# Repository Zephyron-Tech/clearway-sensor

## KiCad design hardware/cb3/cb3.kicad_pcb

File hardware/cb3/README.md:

# CB3 – nosná deska ClearWay v3 (KiCad 10)

Kompletní návrh desky do skříně střešního skeneru v3: schéma, plošný spoj a výrobní data. Popis funkce, bloků a pinů: [configurator/docs/v3-deska.md](../../configurator/docs/v3-deska.md).

> **Stav: rev. B, prototyp.** Schéma i deska prošly kontrolami (ERC 0 chyb, DRC 0 nespojení a 0 kolizí). Návrh vznikl automaticky ze zapojení podle datasheetů a deska je vedená autorouterem. **Před objednávkou ho musí zkontrolovat člověk s praxí v návrhu DPS**, viz [Co zkontrolovat před výrobou](#co-zkontrolovat-před-výrobou).

## Deska

| | |
|---|---|
| Rozměr | 242 × 162 mm, 1,6 mm, obrys s výřezy pro sloupky víka a 4 otvory M3 |
| Vrstvy | 4: F.Cu signály, In1.Cu zem, In2.Cu napájení (VIN_P, 5 V) a signály, B.Cu signály a zem |
| Součástky | 214 (90 C, 51 R, 13 IO, CM5, ZED-F9R, M.2 modem …). Nahoře velké díly, **dole 70 pasivních součástek** (oboustranné osazení) |
| Spoje | 8,8 m spojů, ~500 prokovů 0,5/0,25 mm |
| Pravidla | min. spoj 0,1 mm, mezera 0,125 mm, vrták 0,2 mm (běžná 4vrstvá výroba JLCPCB/PCBWay) |
| Třídy sítí (spoj / mezera) | Default 0,13 / 0,125 mm; Diff (Ethernet, USB) 0,2 / 0,125; Power 0,4 / 0,15; Power12 0,8 / 0,2; HV (vstup) 1,0 / 0,2; Switch (uzly měničů) 0,8 / 0,2 |

Spodní strana: [cb3-bottom.png](cb3-bottom.png), pohled 3D: [cb3-iso.png](cb3-iso.png).

## Výrobní data

Složka [vyroba/](vyroba/):

| Soubor | Co to je |
|---|---|
| `cb3-gerber.zip` | Gerber všech 4 vrstev mědi, masky, pasty, potisku a obrysu + vrtání Excellon (PTH a NPTH zvlášť). Tohle se nahraje výrobci. |
| `cb3-osazeni.csv` | souřadnice pro osazovací automat (obě strany, 201 položek; montážní otvory a testovací plošky se neosazují) |
| `cb3-kusovnik.csv` | kusovník seskupený podle hodnoty, pouzdra a typu (sloupec MPN) |
| `cb3-schema.pdf` | schéma, 6 listů |
| `cb3-osazeni-top.pdf` | osazovací výkres horní strany |

Znovu vygenerovat (po změně v KiCadu):

```bash
sh configurator/scripts/kicad/fab.sh
```

**Objednávka u JLCPCB (příklad):** 4 vrstvy, 1,6 mm, standardní skladba JLC04161H-7628, HASL nebo ENIG (ENIG doporučené kvůli jemné rozteči CM5 a M.2). CM5, modul ZED-F9R a modem EM05-G je levnější dodat a osadit ručně.

## Co v projektu je

| Soubor | Obsah |
|---|---|
| `cb3.kicad_pro` | projekt a třídy sítí |
| `cb3.kicad_sch` + `napajeni`, `vypocet`, `site`, `radio`, `obsluha` | přehledový list a 5 listů bloků |
| `cb3.kicad_pcb` | deska |
| `cb3.kicad_sym`, `cb3.pretty/` | vlastní symboly (KSZ8795CLX, ZED-F9R, TPS1H100A, CM5) a pouzdra (CM5 z referenčního projektu Raspberry Pi, M.2 Key B) |
| `netlist.json` | zapojení po vývodech, ze kterého vzniká schéma i deska |

## Jak deska vznikla (skripty v `configurator/scripts/kicad/`)

1. `cb3-design.mjs`: zapojení všech součástek podle doporučených zapojení z datasheetů (zdroje v hlavičce souboru).
2. `gen-full.mjs`: schéma a `netlist.json`. ERC 0 chyb.
3. `gen-pcb-full.py place`: rozmístění (konektory u otvorů ve skříni, pasivy u svých IO, část na spodní straně), zóny a zakázané oblasti.
4. Freerouting 1.9 (export DSN / import SES), pak `finish-route.py`: vlastní dotahovač (A* na mřížce 0,1 mm) na posledních několik spojů a opravy kolizí.
5. `gen-pcb-full.py pour`: rozlití zemí a zón, `link-pcb.py`: svázání pouzder se symboly schématu (funguje F8 Aktualizovat DPS ze schématu).
6. `fab.sh`: výrobní data.
7. `export-3d.py`: polohy a rozměry součástek do 3D modelu v konfigurátoru (`src/cad/board-v3-pcb.js`).
8. `export-texture.py`: měď, plošky a potisk obou stran jako textura desky v konfigurátoru (`public/models/cb3-top.jpg`, `cb3-bottom.jpg`).

**Od teď je zdrojem pravdy projekt KiCad.** Úpravy dělat v KiCadu ručně; generátory desku přepíší (rozmístění a vedení by se ztratilo).

## Kontroly

- **ERC:** 0 chyb, 0 varování.
- **DRC:** 0 nespojených sítí, 0 kolizí, 0 zkratů. Zbývá jen kosmetika potisku (popisky se překrývají nebo leží na ploškách, ~90 varování; výrobce potisk na ploškách ořízne).
- **Parita DPS ↔ schéma:** 17 varování, všechny jsou upevňovací a stínicí plošky konektorů (MP, SH, S1, S2), které jsou záměrně na zemi a symbol je nemá.

## Co zkontrolovat před výrobou

Seřazené podle důležitosti.

1. **Zemní vrstva In1 není souvislá.** Autorouter jí vedl asi 3,4 m signálů. Návratové cesty, rušení a GNSS tím trpí. Nejlepší oprava je převést tyto spoje na F/B/In2 a In1 nechat jako celistvou zem.
2. **Diferenciální páry** (Ethernet T1–T5, USB k modemu a servisu) jsou vedené bez řízené impedance a bez vyrovnání délek. Pro 100 Mb/s a USB 2.0 by to fungovat mělo, ale páry je potřeba projít a podle skladby výrobce nastavit šířku/mezeru na 100 Ω a 90 Ω.
3. **RF GNSS** (J7 → ZED-F9R RF_IN): spoj má mít 50 Ω (koplanár se zemí) a pod modulem souvislou zem.
4. **Větev 12 V je jen snižující** (TPS54560B). Při napětí vozu pod ~13 V (12V vůz, startování) klesne pod 12 V. Ověřit, že skenery a lidar snesou rozsah 9–12 V, jinak měnič buck-boost.
5. **Pouzdro M.2 Key B** je odvozené z pouzdra M-key z referenčního projektu CM5 (posunutý klíč). Před objednáním porovnat s výkresem TE 2199230-3.
6. **Hodnoty pasivních součástek** jsou podle referenčních návrhů TI. U U2 (12 V) je kompenzace přepočítaná, ověřit v TI WEBENCH nebo výpočtem.
7. **Teplo:** U3 (5 V / 5 A) a U2 potřebují tepelné prokovy do zemních vrstev, zkontrolovat počet pod plochou pouzdra.
8. **Ethernet CM5 ↔ přepínač** jde přes dva transformátory zády k sobě (T4, T5). Funkční, ale ověřit proti aplikační poznámce Microchip.
9. **Potisk:** přesunout překrývající se popisky (kosmetika).

## Jak to otevřít

KiCad je v `~/Applications/KiCad` (instalace přes Homebrew chtěla heslo správce). Otevřít `cb3.kicad_pro`, při prvním spuštění potvrdit výchozí knihovny.

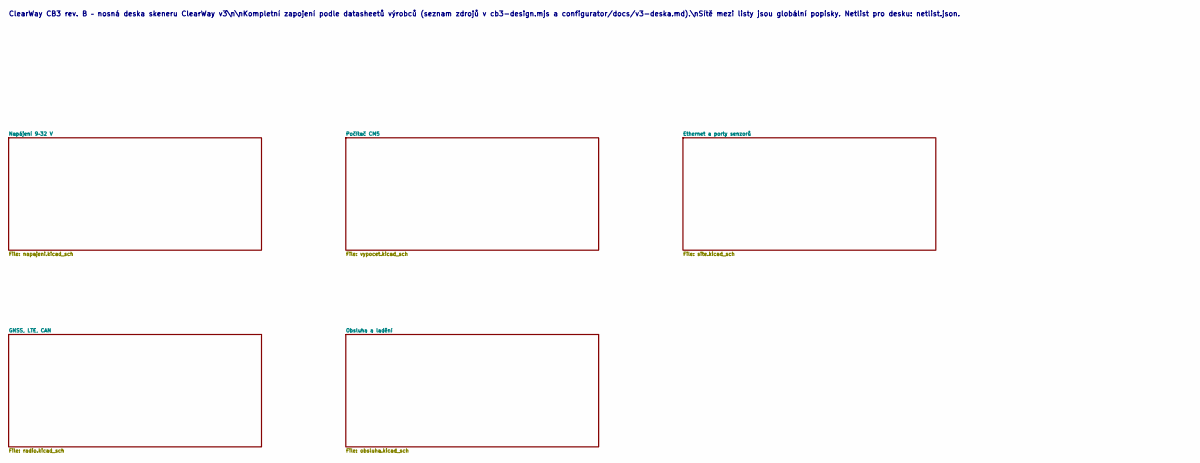
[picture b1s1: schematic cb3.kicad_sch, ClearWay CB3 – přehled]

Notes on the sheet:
ClearWay CB3 rev. B – nosná deska skeneru ClearWay v3\n\nKompletní zapojení podle datasheetů výrobců (seznam zdrojů v cb3-design.mjs a configurator/docs/v3-deska.md).\nSítě mezi listy jsou globální popisky. Netlist pro desku: netlist.json.

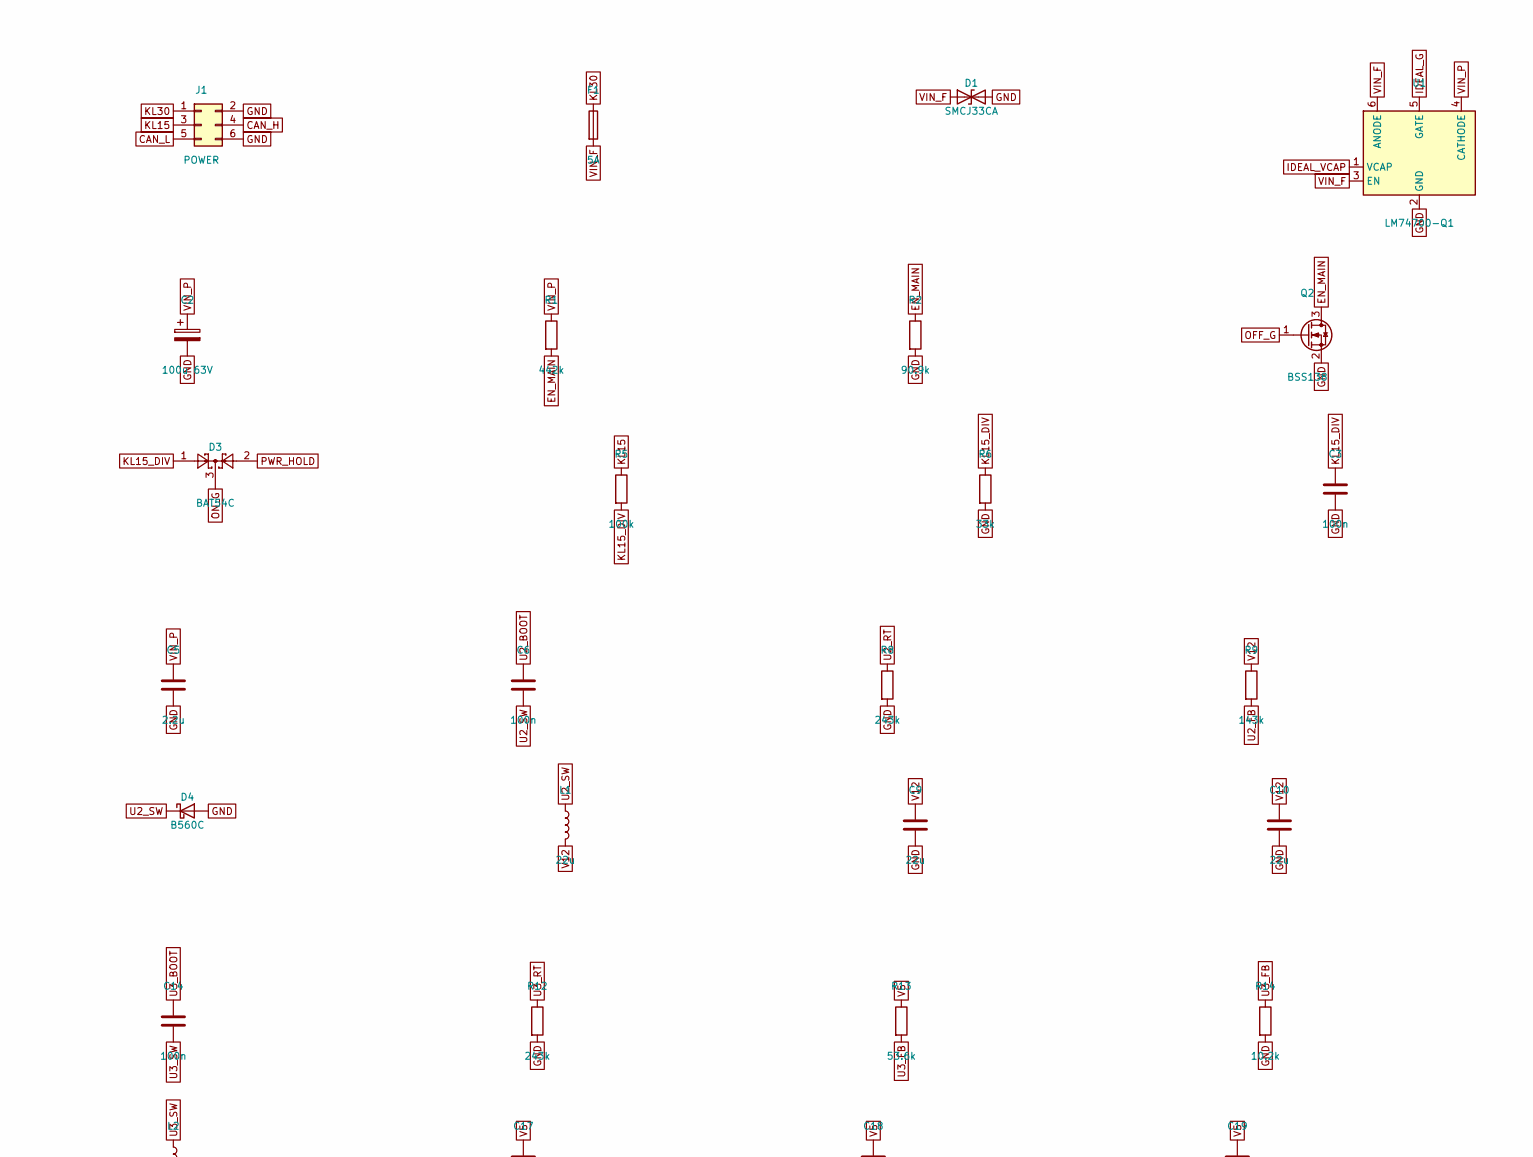
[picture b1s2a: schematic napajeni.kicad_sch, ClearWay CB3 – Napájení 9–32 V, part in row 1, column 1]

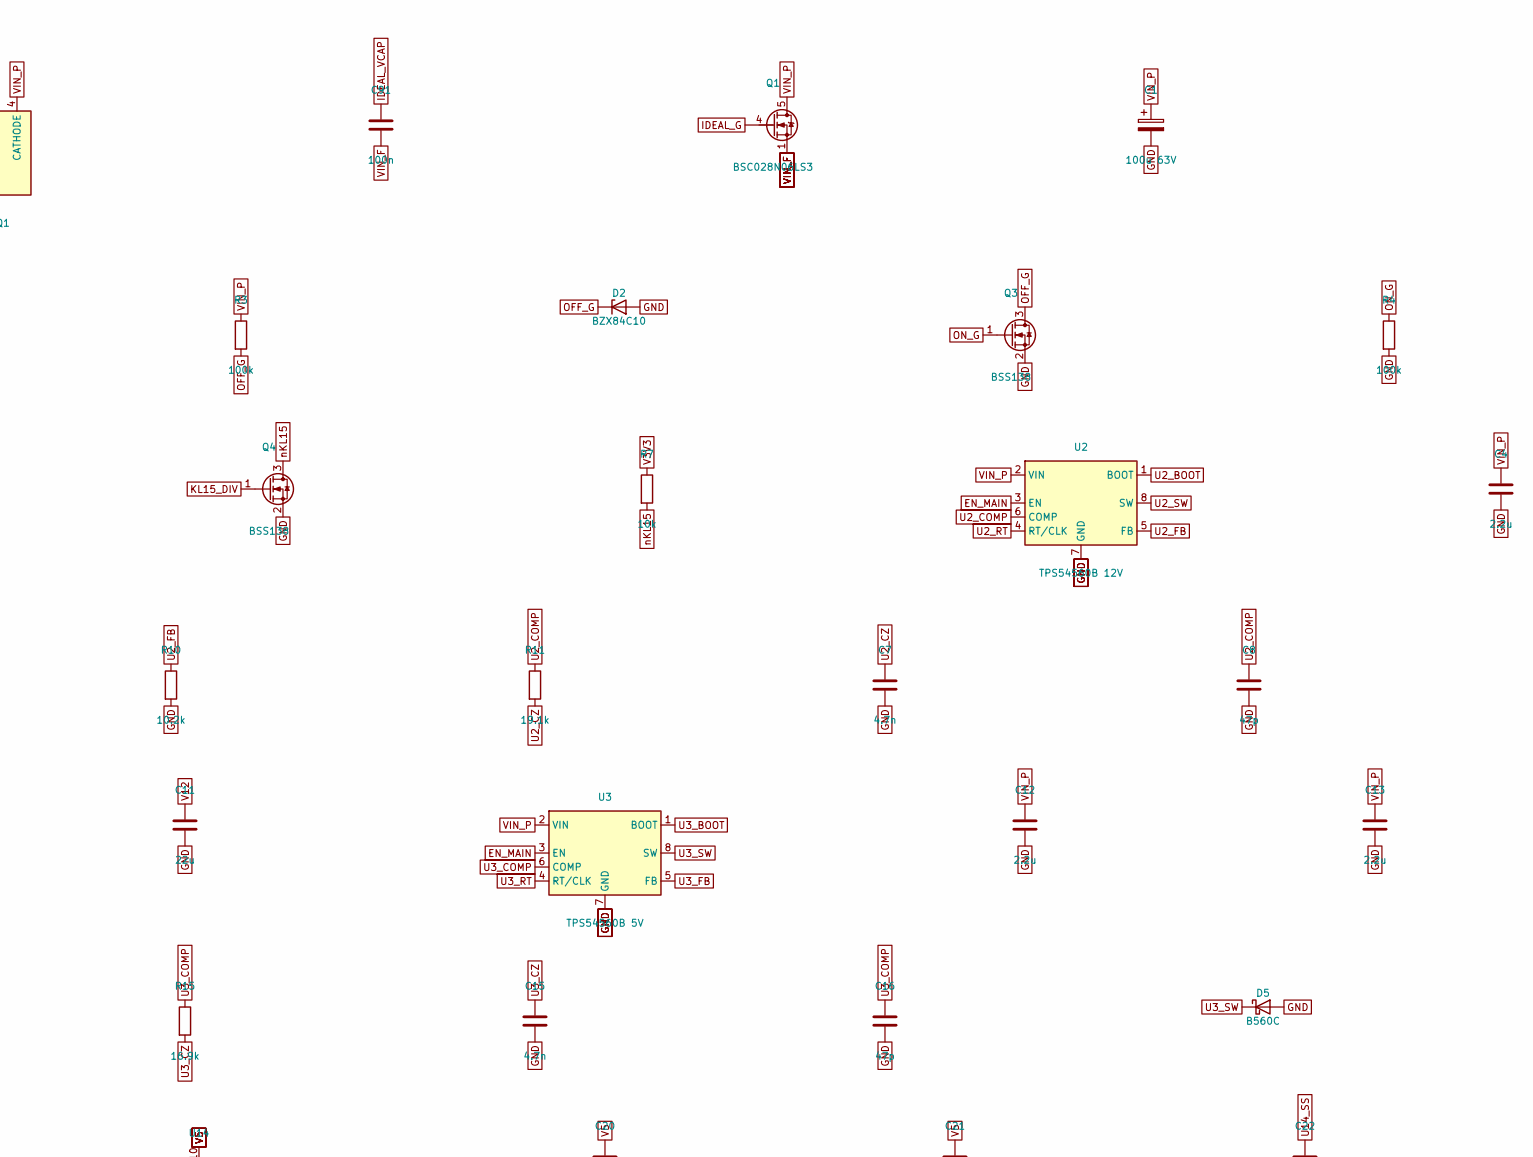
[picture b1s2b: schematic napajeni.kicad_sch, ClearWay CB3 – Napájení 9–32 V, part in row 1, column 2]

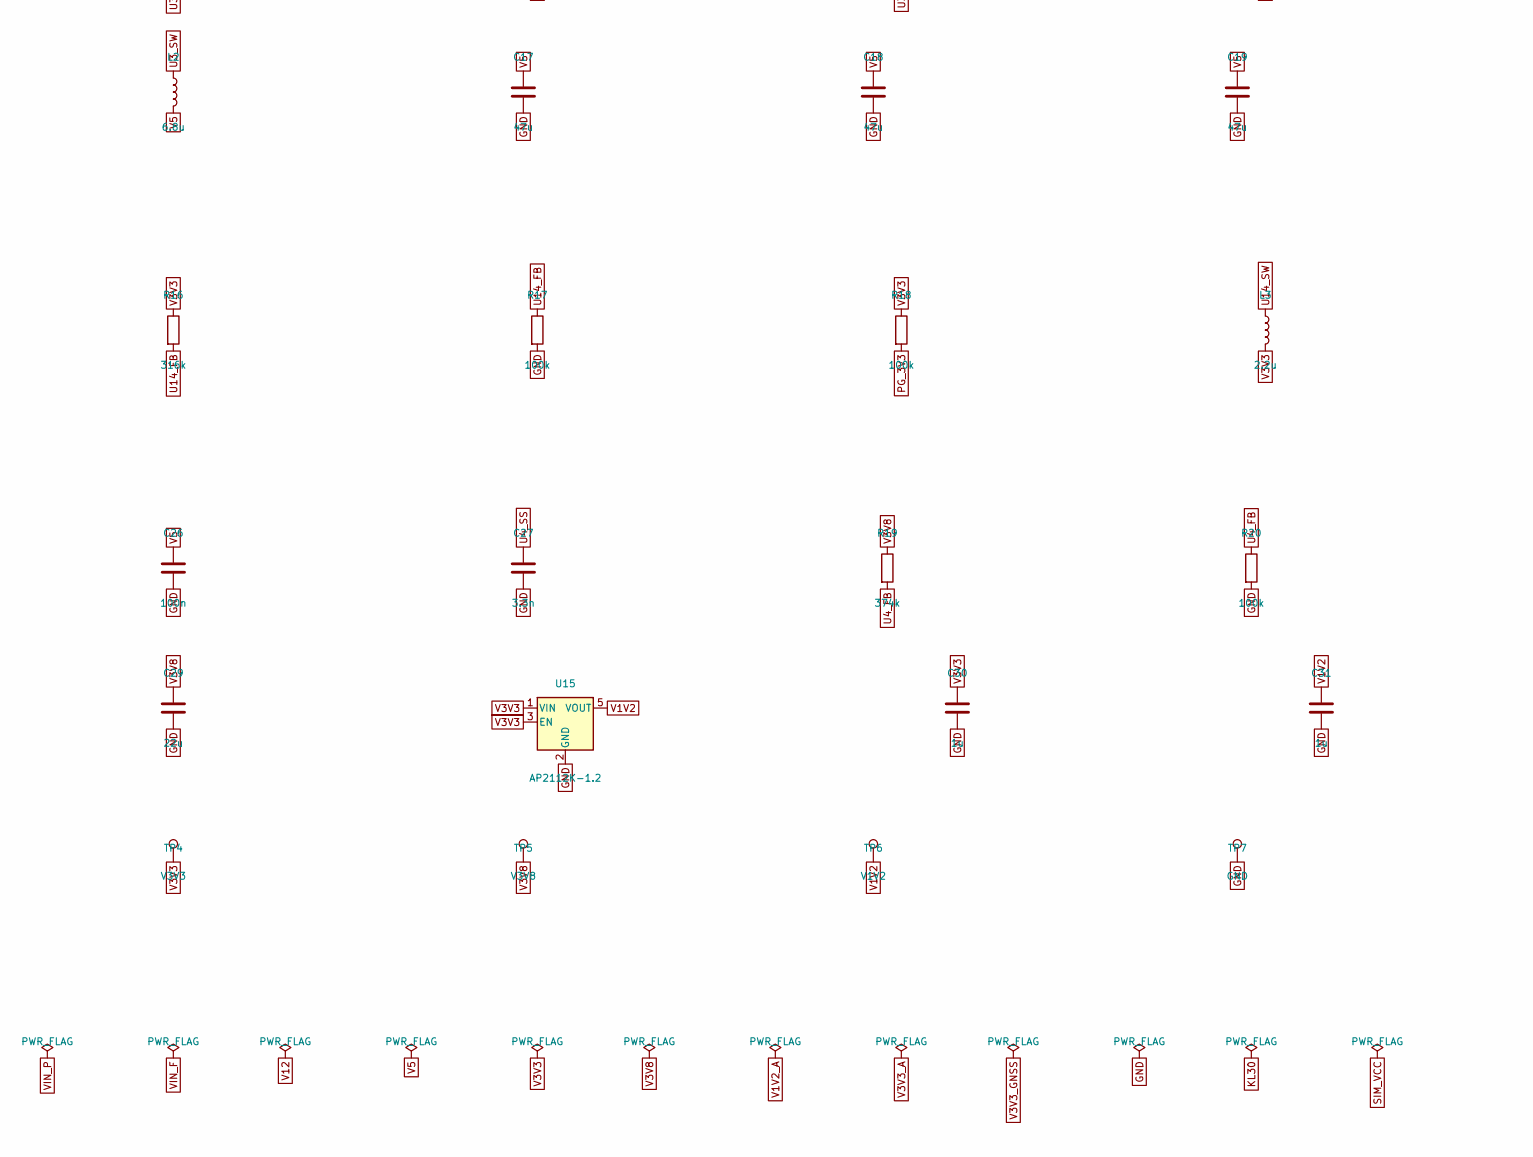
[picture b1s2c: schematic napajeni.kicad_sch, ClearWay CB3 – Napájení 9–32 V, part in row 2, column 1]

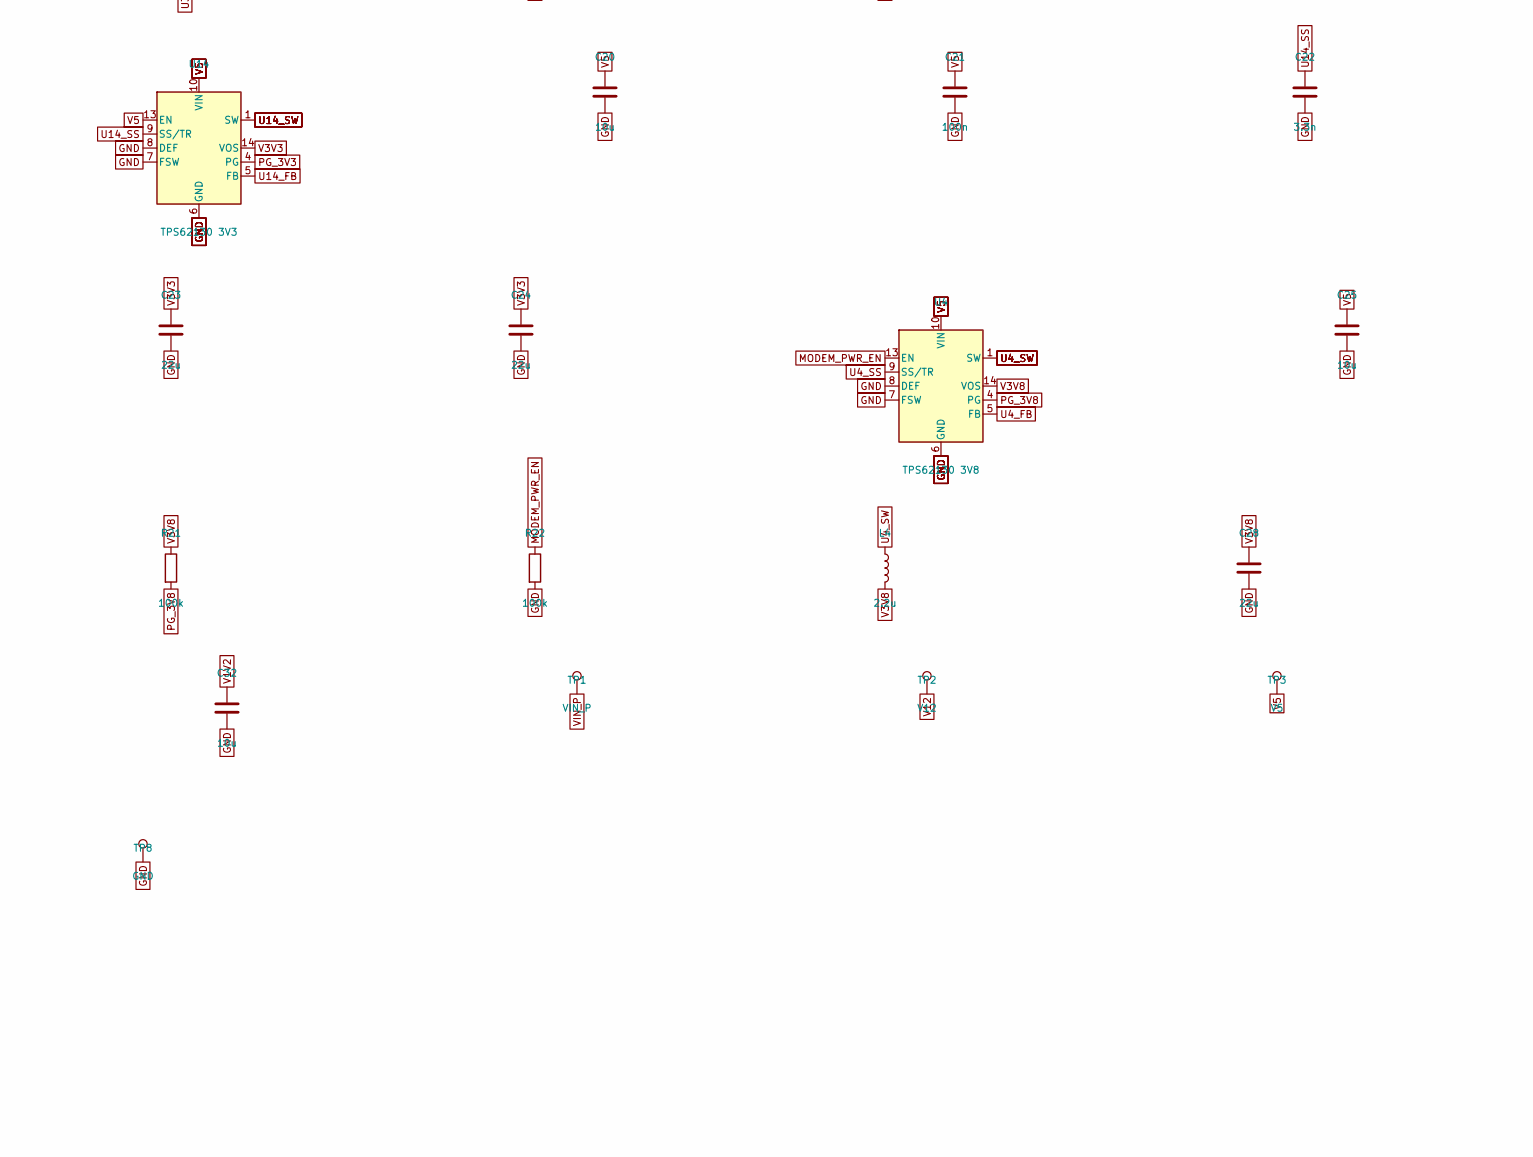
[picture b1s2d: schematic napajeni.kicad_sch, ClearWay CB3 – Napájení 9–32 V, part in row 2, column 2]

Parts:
C1, C2: 100u 63V; CP_Elec_10x10.5; MPN Panasonic EEH-ZK1J101P (hybridní polyme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
C3: 100n; C_0402_1005Metric; MPN keramický kondenzátor 100n X7R
C4, C5, C12, C13: 2.2u; C_1210_3225Metric; MPN kondenzátor 2,2 µF 100 V X7R 1210
C6, C14, C21, C26: 100n; C_0603_1608Metric; MPN keramický kondenzátor 100n X7R
C7, C15: 4.7n; C_0402_1005Metric; MPN keramický kondenzátor 4.7n X7R
C8, C16: 47p; C_0402_1005Metric; MPN kondenzátor 47 pF C0G
C9, C10, C11: 22u; C_1210_3225Metric; MPN kondenzátor 22 µF 25 V X7R 1210
C17, C18, C19: 47u; C_1210_3225Metric; MPN kondenzátor 47 µF 10 V X5R 1210
C20, C25: 10u; C_1210_3225Metric; MPN kondenzátor 10 µF 25 V X7R 1210
C22, C27: 3.3n; C_0402_1005Metric; MPN keramický kondenzátor 3.3n X7R
C23, C24, C28, C29: 22u; C_0805_2012Metric; MPN kondenzátor 22 µF 10 V X5R 0805
C30, C31: 1u; C_0603_1608Metric; MPN keramický kondenzátor 1u X7R
C32: 10u; C_0805_2012Metric; MPN kondenzátor 10 µF 10 V X5R 0805
C91: 100n; C_0603_1608Metric; MPN kondenzátor 100 nF 25 V X7R 0603 (VCAP–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
D1: SMCJ33CA; D_SMC; MPN Littelfuse SMCJ33CA (obousměrný, 1500 W)
D2: BZX84C10; SOT-23; MPN Nexperia BZX84-C10
D3: BAT54C; SOT-23; MPN Nexperia BAT54C
D4, D5: B560C; D_SMC; MPN Diodes B560C-13-F (60 V, 5 A)
F1: 5A; Fuse_1206_3216Metric; MPN Littelfuse 0466005.NR (5 A, 1206) – ově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
J1: POWER; Molex_Micro-Fit_3.0_43045-0612_2x03_P3.00mm_Vertical; MPN Molex 43045-0612
L1: 22u; L_Coilcraft_XAL1010-XXX; MPN Coilcraft XAL1010-223MEB
L2: 6.8u; L_Coilcraft_XAL1010-XXX; MPN Coilcraft XAL1010-682MEB
L3, L4: 2.2u; L_Coilcraft_XAL4020-XXX; MPN Coilcraft XAL4020-222MEC
Q1: BSC028N06LS3; TDSON-8-1; MPN Infineon BSC028N06LS3 (60 V, 2,8 mΩ)
Q2, Q3, Q4: BSS138; SOT-23; MPN onsemi BSS138
R1: 442k; R_0402_1005Metric; MPN rezistor 442k 1 % 0402
R2: 90.9k; R_0402_1005Metric; MPN rezistor 90.9k 1 % 0402
R3, R4, R5, R17, R18, R20, R21, R22: 100k; R_0402_1005Metric; MPN rezistor 100k 1 % 0402
R6: 33k; R_0402_1005Metric; MPN rezistor 33k 1 % 0402
R7: 10k; R_0402_1005Metric; MPN rezistor 10k 1 % 0402
R8, R12: 243k; R_0402_1005Metric; MPN rezistor 243k 1 % 0402
R9: 143k; R_0402_1005Metric; MPN rezistor 143k 1 % 0402
R10, R14: 10.2k; R_0402_1005Metric; MPN rezistor 10.2k 1 % 0402
R11: 19.1k; R_0402_1005Metric; MPN rezistor 19.1k 1 % 0402
R13: 53.6k; R_0402_1005Metric; MPN rezistor 53.6k 1 % 0402
R15: 16.9k; R_0402_1005Metric; MPN rezistor 16.9k 1 % 0402
R16: 316k; R_0402_1005Metric; MPN rezistor 316k 1 % 0402
R19: 374k; R_0402_1005Metric; MPN rezistor 374k 1 % 0402
TP1: VIN_P; TestPoint_Pad_D1.5mm; MPN testovací ploška
TP2: V12; TestPoint_Pad_D1.5mm; MPN testovací ploška
TP3: V5; TestPoint_Pad_D1.5mm; MPN testovací ploška
TP4: V3V3; TestPoint_Pad_D1.5mm; MPN testovací ploška
TP5: V3V8; TestPoint_Pad_D1.5mm; MPN testovací ploška
TP6: V1V2; TestPoint_Pad_D1.5mm; MPN testovací ploška
TP7, TP8: GND; TestPoint_Pad_D1.5mm; MPN testovací ploška
U1: LM74700-Q1; SOT-23-6; MPN TI LM74700QDBVRQ1
U2: TPS54560B 12V; Texas_R-PDSO-G8_EP2.95x4.9mm_Mask2.4x3.1mm_ThermalVias; MPN TI TPS54560BDDAR
U3: TPS54560B 5V; Texas_R-PDSO-G8_EP2.95x4.9mm_Mask2.4x3.1mm_ThermalVias; MPN TI TPS54560BDDAR
U4: TPS62130 3V8; VQFN-16-1EP_3x3mm_P0.5mm_EP1.68x1.68mm_ThermalVias; MPN TI TPS62130RGTR
U14: TPS62130 3V3; VQFN-16-1EP_3x3mm_P0.5mm_EP1.68x1.68mm_ThermalVias; MPN TI TPS62130RGTR
U15: AP2112K-1.2; SOT-23-5; MPN Diodes AP2112K-1.2TRG1

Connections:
CAN_H: J1.4; also elsewhere on the board
CAN_L: J1.5; also elsewhere on the board
EN_MAIN: Q2.3 (D), R1.2, R2.1, U2.3 (EN), U3.3 (EN)
GND: C1.2, C2.2, C3.2, C4.2, C5.2, C7.2, C8.2, C9.2, C10.2, C11.2, C12.2, C13.2, C15.2, C16.2, C17.2, C18.2, C19.2, C20.2, C21.2, C22.2, C23.2, C24.2, C25.2, C26.2, C27.2, C28.2, C29.2, C30.2, C31.2, C32.2, D1.2 (A2), D2.1 (A), D4.2 (A), D5.2 (A), J1.2, J1.6, Q2.2 (S), Q3.2 (S), Q4.2 (S), R2.2, R4.2, R6.2, R8.2, R10.2, R12.2, R14.2, R17.2, R20.2, R22.2, TP7.1, TP8.1, U1.2 (GND), U2.7 (GND), U2.9 (GND), U3.7 (GND), U3.9 (GND), U4.6 (GND), U4.7 (FSW), U4.8 (DEF), U4.15 (GND), U4.16 (GND), U4.17 (GND), U14.6 (GND), U14.7 (FSW), U14.8 (DEF), U14.15 (GND), U14.16 (GND), U14.17 (GND), U15.2 (GND); also elsewhere on the board
IDEAL_G: Q1.4 (G), U1.5 (GATE)
IDEAL_VCAP: C91.1, U1.1 (VCAP)
KL15: J1.3, R5.1
KL15_DIV: C3.1, D3.1, Q4.1 (G), R5.2, R6.1
KL30: F1.1, J1.1
MODEM_PWR_EN: R22.1, U4.13 (EN); also elsewhere on the board
OFF_G: D2.3 (K), Q2.1 (G), Q3.3 (D), R3.2
ON_G: D3.3, Q3.1 (G), R4.1
PG_3V3: R18.2, U14.4 (PG)
PG_3V8: R21.2, U4.4 (PG)
PWR_HOLD: D3.2; also elsewhere on the board
U2_BOOT: C6.1, U2.1 (BOOT)
U2_COMP: C8.1, R11.1, U2.6 (COMP)
U2_CZ: C7.1, R11.2
U2_FB: R9.2, R10.1, U2.5 (FB)
U2_RT: R8.1, U2.4 (RT/CLK)
U2_SW: C6.2, D4.1 (K), L1.1, U2.8 (SW)
U3_BOOT: C14.1, U3.1 (BOOT)
U3_COMP: C16.1, R15.1, U3.6 (COMP)
U3_CZ: C15.1, R15.2
U3_FB: R13.2, R14.1, U3.5 (FB)
U3_RT: R12.1, U3.4 (RT/CLK)
U3_SW: C14.2, D5.1 (K), L2.1, U3.8 (SW)
U4_FB: R19.2, R20.1, U4.5 (FB)
U4_SS: C27.1, U4.9 (SS/TR)
U4_SW: L4.1, U4.1 (SW), U4.2 (SW), U4.3 (SW)
U14_FB: R16.2, R17.1, U14.5 (FB)
U14_SS: C22.1, U14.9 (SS/TR)
U14_SW: L3.1, U14.1 (SW), U14.2 (SW), U14.3 (SW)
V1V2: C31.1, C32.1, TP6.1, U15.5 (VOUT); also elsewhere on the board
V3V3: C23.1, C24.1, C30.1, L3.2, R7.1, R16.1, R18.1, TP4.1, U14.14 (VOS), U15.1 (VIN), U15.3 (EN); also elsewhere on the board
V3V8: C28.1, C29.1, L4.2, R19.1, R21.1, TP5.1, U4.14 (VOS); also elsewhere on the board
V5: C17.1, C18.1, C19.1, C20.1, C21.1, C25.1, C26.1, L2.2, R13.1, TP3.1, U4.10 (VIN), U4.11 (VIN), U4.12 (VIN), U14.10 (VIN), U14.11 (VIN), U14.12 (VIN), U14.13 (EN); also elsewhere on the board
V12: C9.1, C10.1, C11.1, L1.2, R9.1, TP2.1; also elsewhere on the board
VIN_F: C91.2, D1.1 (A1), F1.2, Q1.1 (S), Q1.2 (S), Q1.3 (S), U1.3 (EN), U1.6 (ANODE)
VIN_P: C1.1, C2.1, C4.1, C5.1, C12.1, C13.1, Q1.5 (D), R1.1, R3.1, TP1.1, U1.4 (CATHODE), U2.2 (VIN), U3.2 (VIN)
nKL15: Q4.3 (D), R7.2; also elsewhere on the board

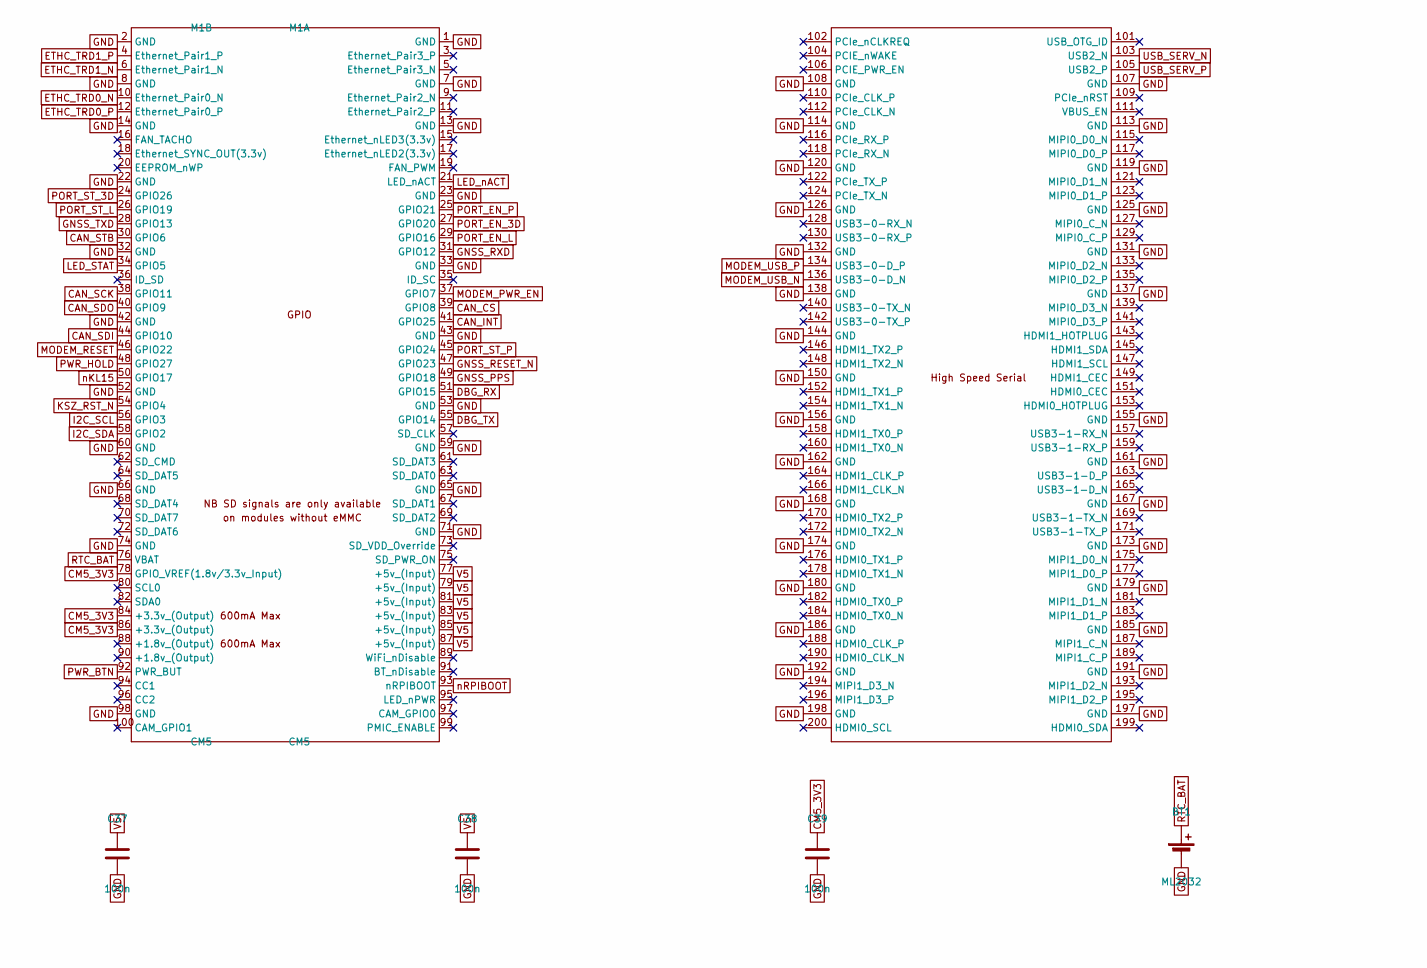
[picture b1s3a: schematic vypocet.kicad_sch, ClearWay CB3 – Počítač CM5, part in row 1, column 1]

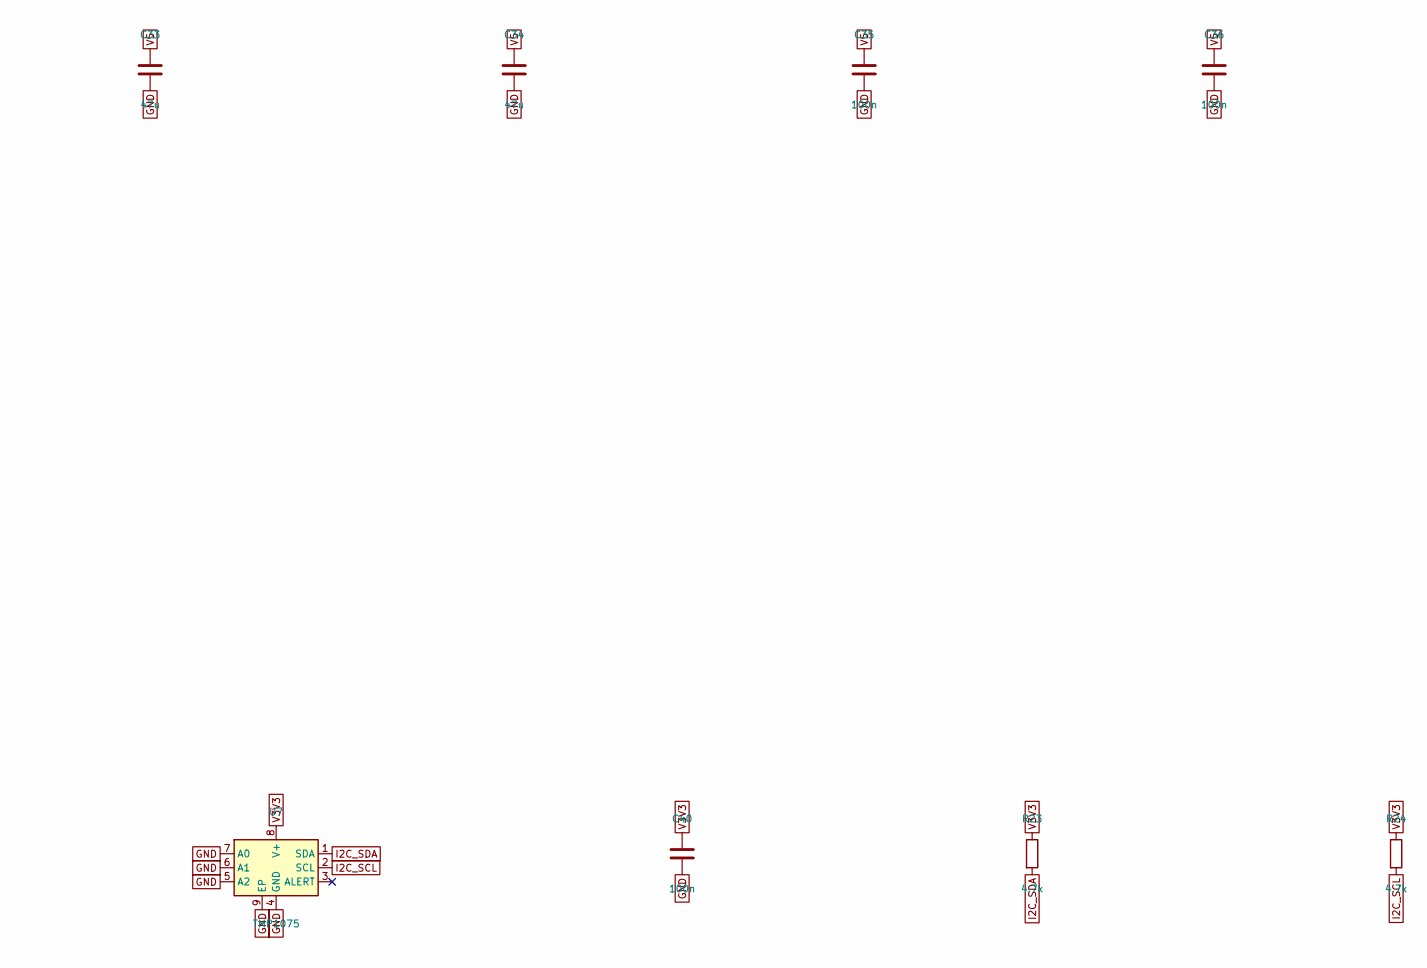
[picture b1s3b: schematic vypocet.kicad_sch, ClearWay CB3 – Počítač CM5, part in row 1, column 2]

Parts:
BT1: ML2032; BatteryHolder_Keystone_3034_1x20mm; MPN Keystone 3034 + Maxell ML2032 (dobíjecí)
C33, C34: 47u; C_1210_3225Metric; MPN kondenzátor 47 µF 10 V X5R 1210
C35, C36, C37, C38, C39, C40: 100n; C_0402_1005Metric; MPN keramický kondenzátor 100n X7R
M1: CM5; Raspberry-Pi-5-Compute-Module; MPN Raspberry Pi CM5104032 (CM5, 4 GB, 32 G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
R23, R24: 4.7k; R_0402_1005Metric; MPN rezistor 4.7k 1 % 0402
U7: TMP1075; Texas_DSG0008A_WSON-8-1EP_2x2mm_P0.5mm_EP0.9x1.6mm_ThermalV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; MPN TI TMP1075DSGR

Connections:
CAN_CS: M1.39 (GPIO8); also elsewhere on the board
CAN_INT: M1.41 (GPIO25); also elsewhere on the board
CAN_SCK: M1.38 (GPIO11); also elsewhere on the board
CAN_SDI: M1.44 (GPIO10); also elsewhere on the board
CAN_SDO: M1.40 (GPIO9); also elsewhere on the board
CAN_STB: M1.30 (GPIO6); also elsewhere on the board
CM5_3V3: C39.1, M1.78 (GPIO_VREF(1.8v/3.3v_Input)), M1.84 (+3.3v_(Output)), M1.86 (+3.3v_(Output)); also elsewhere on the board
DBG_RX: M1.51 (GPIO15); also elsewhere on the board
DBG_TX: M1.55 (GPIO14); also elsewhere on the board
ETHC_TRD0_N: M1.10 (Ethernet_Pair0_N); also elsewhere on the board
ETHC_TRD0_P: M1.12 (Ethernet_Pair0_P); also elsewhere on the board
ETHC_TRD1_N: M1.6 (Ethernet_Pair1_N); also elsewhere on the board
ETHC_TRD1_P: M1.4 (Ethernet_Pair1_P); also elsewhere on the board
GND: BT1.2 (-), C33.2, C34.2, C35.2, C36.2, C37.2, C38.2, C39.2, C40.2, M1.1 (GND), M1.2 (GND), M1.7 (GND), M1.8 (GND), M1.13 (GND), M1.14 (GND), M1.22 (GND), M1.23 (GND), M1.32 (GND), M1.33 (GND), M1.42 (GND), M1.43 (GND), M1.52 (GND), M1.53 (GND), M1.59 (GND), M1.60 (GND), M1.65 (GND), M1.66 (GND), M1.71 (GND), M1.74 (GND), M1.98 (GND), M1.107 (GND), M1.108 (GND), M1.113 (GND), M1.114 (GND), M1.119 (GND), M1.120 (GND), M1.125 (GND), M1.126 (GND), M1.131 (GND), M1.132 (GND), M1.137 (GND), M1.138 (GND), M1.144 (GND), M1.150 (GND), M1.155 (GND), M1.156 (GND), M1.161 (GND), M1.162 (GND), M1.167 (GND), M1.168 (GND), M1.173 (GND), M1.174 (GND), M1.179 (GND), M1.180 (GND), M1.185 (GND), M1.186 (GND), M1.191 (GND), M1.192 (GND), M1.197 (GND), M1.198 (GND), U7.4 (GND), U7.5 (A2), U7.6 (A1), U7.7 (A0), U7.9 (EP); also elsewhere on the board
GNSS_PPS: M1.49 (GPIO18); also elsewhere on the board
GNSS_RESET_N: M1.47 (GPIO23); also elsewhere on the board
GNSS_RXD: M1.31 (GPIO12); also elsewhere on the board
GNSS_TXD: M1.28 (GPIO13); also elsewhere on the board
I2C_SCL: M1.56 (GPIO3), R24.2, U7.2 (SCL)
I2C_SDA: M1.58 (GPIO2), R23.2, U7.1 (SDA)
KSZ_RST_N: M1.54 (GPIO4); also elsewhere on the board
LED_STAT: M1.34 (GPIO5); also elsewhere on the board
LED_nACT: M1.21 (LED_nACT); also elsewhere on the board
MODEM_PWR_EN: M1.37 (GPIO7); also elsewhere on the board
MODEM_RESET: M1.46 (GPIO22); also elsewhere on the board
MODEM_USB_N: M1.136 (USB3-0-D_N); also elsewhere on the board
MODEM_USB_P: M1.134 (USB3-0-D_P); also elsewhere on the board
PORT_EN_3D: M1.27 (GPIO20); also elsewhere on the board
PORT_EN_L: M1.29 (GPIO16); also elsewhere on the board
PORT_EN_P: M1.25 (GPIO21); also elsewhere on the board
PORT_ST_3D: M1.24 (GPIO26); also elsewhere on the board
PORT_ST_L: M1.26 (GPIO19); also elsewhere on the board
PORT_ST_P: M1.45 (GPIO24); also elsewhere on the board
PWR_BTN: M1.92 (PWR_BUT); also elsewhere on the board
PWR_HOLD: M1.48 (GPIO27); also elsewhere on the board
RTC_BAT: BT1.1 (+), M1.76 (VBAT)
USB_SERV_N: M1.103 (USB2_N); also elsewhere on the board
USB_SERV_P: M1.105 (USB2_P); also elsewhere on the board
V3V3: C40.1, R23.1, R24.1, U7.8 (V+); also elsewhere on the board
V5: C33.1, C34.1, C35.1, C36.1, C37.1, C38.1, M1.77 (+5v_(Input)), M1.79 (+5v_(Input)), M1.81 (+5v_(Input)), M1.83 (+5v_(Input)), M1.85 (+5v_(Input)), M1.87 (+5v_(Input)); also elsewhere on the board
nKL15: M1.50 (GPIO17); also elsewhere on the board
nRPIBOOT: M1.93 (nRPIBOOT); also elsewhere on the board
